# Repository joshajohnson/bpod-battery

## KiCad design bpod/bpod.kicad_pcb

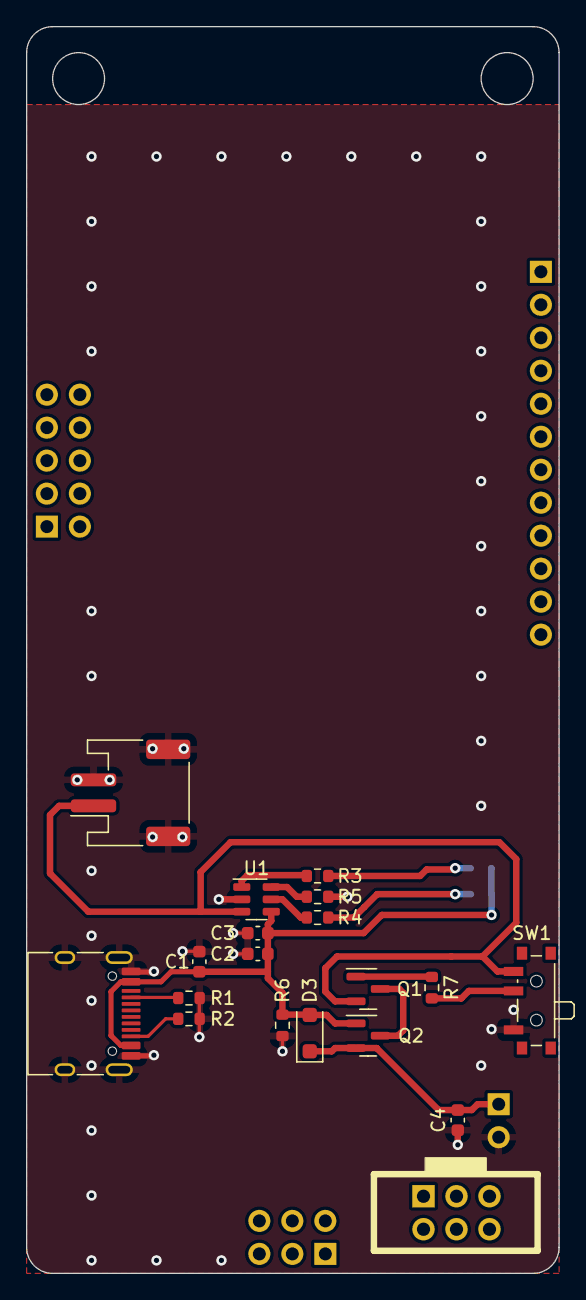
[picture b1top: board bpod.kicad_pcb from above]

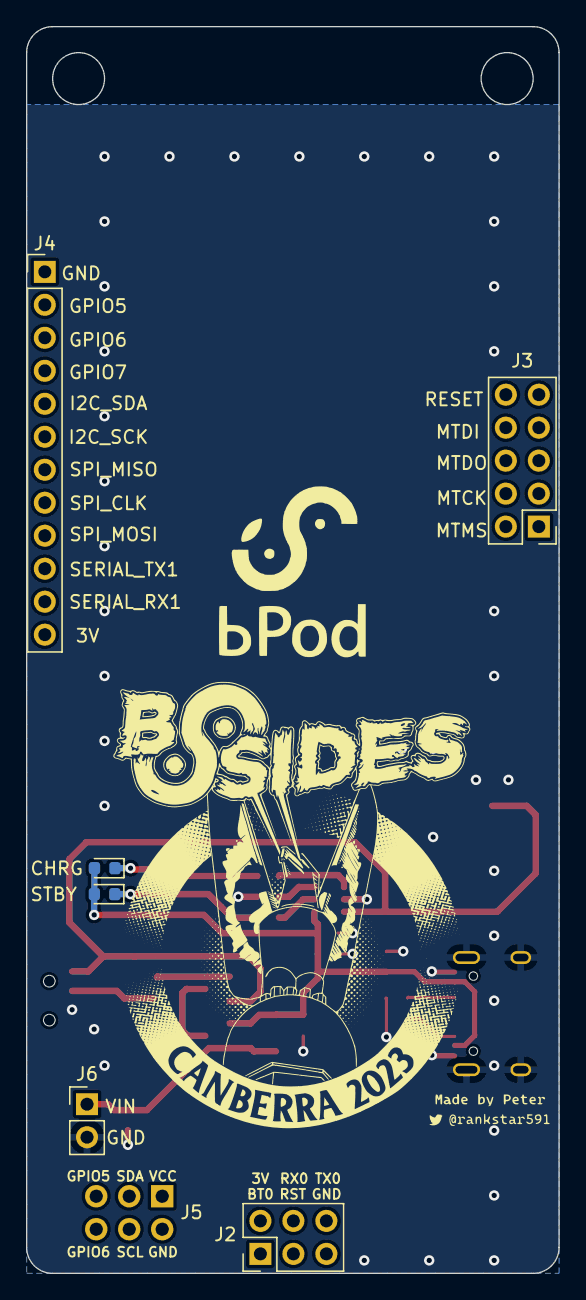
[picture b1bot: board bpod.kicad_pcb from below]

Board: 2 copper layers, 41.0 x 96.0 mm, 28 parts (9 on the bottom side), 14 nets.

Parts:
C1, C4: 4u7; C_0603_1608Metric
C2: 10u; C_0603_1608Metric
C3: 1u; C_0603_1608Metric
D1: GRN; LED_0603_1608Metric
D2: RED; LED_0603_1608Metric
D3: MBR120; D_SOD-123F
J1: USB_C_Receptacle_USB2.0; USB_C_Receptacle_HRO_TYPE-C-31-M-12
J2: PROGRAM; PinHeader_2x03_P2.54mm_Vertical
J3: DEBUG; PinHeader_2x05_P2.54mm_Vertical
J4: Conn_01x12; PinHeader_1x12_P2.54mm_Vertical
J5: SAO; Simple_Addon_v2-BADGE-2x3
J6: Conn_01x02; PinHeader_1x02_P2.54mm_Vertical
J7: JST_PH2; JST_PH_S2B-PH-SM4-TB_1x02-1MP_P2.00mm_Horizontal
Q1, Q2: DMP2045U; SOT-23
R1, R2, R3, R4, R7: 5K1; R_0603_1608Metric
R5: 2K; R_0603_1608Metric
R6: 100K; R_0603_1608Metric
SW1: SLIDE; SW_SPDT_PCM12
U1: TP4057; SOT-23-6
U10: bsides-2023
U11: made_by_peter
U14: bpod-logo

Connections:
+5V: C1.1, C2.1, C3.1, D1.2 (A), D2.2 (A), D3.2 (A), J1.A4 (VBUS), J1.A9 (VBUS), J1.B4 (VBUS), J1.B9 (VBUS), Q2.1 (G), R6.1, U1.4 (VCC)
+BATT: J7.1, Q1.2 (S), SW1.3 (C), U1.3 (BATT)
/VOUT: C4.1, D3.1 (K), J6.1, Q2.2 (S)
GND: C1.2, C2.2, C3.2, C4.2, J1.A1 (GND), J1.A12 (GND), J1.B1 (GND), J1.B12 (GND), J1.S1 (SHIELD), J6.2, J7.2, R1.2, R2.1, R5.1, R6.2, SW1.1 (A), U1.2 (GND)
unnamed: D1.1 (K), R4.2
unnamed: D2.1 (K), R3.2
unnamed: J1.A5 (CC1), R1.1
unnamed: J1.B5 (CC2), R2.2
unnamed: Q1.3 (D), Q2.3 (D)
unnamed: Q1.1 (G), R7.2
unnamed: R7.1, SW1.2 (B)
unnamed: R5.2, U1.6 (PROG)
unnamed: R3.1, U1.1 (nCHRG)
unnamed: R4.1, U1.5 (nSTDBY)

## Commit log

2023-10-07 add files
